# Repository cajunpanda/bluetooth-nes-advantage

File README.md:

# Bluetooth NES Advantage (v2)

Integrated Bluetooth for the NES Advantage (NES-026) arcade stick. It pairs directly with a
Nintendo Switch, an 8BitDo NES Retro Receiver (for a real NES), and PCs, phones, and emulators
over BLE. No case cutting and no added buttons: everything runs from the stick's own controls,
and it charges through the original cable hole.

**[Watch the overview and how-to video](https://youtu.be/xjbFiXHXB24)** for a tour of the mod and
everything below in use.

## Features

- Direct Nintendo Switch pairing (Switch Pro Controller emulation over BT Classic)
- Home, ZL + ZR (the NSO retro menu), ZL, ZR, and Capture — buttons the NES stick never had, on
  Select-held chords, instant and usable mid-game; the chord window is configurable, or off
- 8BitDo NES Retro Receiver support for playing on a real NES
- BLE gamepad mode for PC, Android, SteamOS, Linux, and BlueRetro
- Turbo and slow motion work as normal
- Player-select slider: in BLE mode the stick exposes two gamepads for take-turns play
- Wake on button press from a deep sleep that draws microamps
- Battery life on an 1800 mAh cell: about 17 hours in Switch/Receiver mode, about 37 hours in
  BLE mode, months of standby
- Low input latency: the board adds about 4 ms in Switch/Receiver mode and about 6 ms in BLE mode
- Browser-based configuration and over-the-air firmware updates, no cable needed
- RGB status LEDs, battery level monitoring, 5 V barrel jack charging
- Play while charging (load-share power path)

## Configure and update from your browser

A built-in Web Bluetooth app tests every input, tunes how the stick behaves, and flashes new
firmware over the air with no cable and nothing to install. Put the stick in config mode (hold
A + B + Select for 5 s), open the hosted
**[config page](https://cajunpanda.github.io/bluetooth-nes-advantage/)** in Chrome or Edge, and
connect. Every button, the D-pad, the player-select slider, and the turbo dials light up live as
you use them:

Change transport, button profile, and directional mode and apply over the air, or drop a
`firmware.bin` on the cartridge slot to update. The
[manual](docs/MANUAL.md#configuration-and-firmware-updates) has the full walkthrough.

## How it works

A single custom PCB replaces the controller's cable. A bare ESP32-WROOM-32E reads the original
CD4021 shift registers and presents the stick as a Bluetooth gamepad in one of two modes:

- Switch mode (Bluetooth Classic): emulates a Switch Pro Controller. Pairs directly with a
  Nintendo Switch and with the 8BitDo NES Retro Receiver.
- BLE mode: a standard BLE HID gamepad ("NES Advantage") for PCs, phones, BlueRetro, and
  emulators.

Turbo, slow motion, and the player-select slider all work as originally designed.

## Documentation

Start with the guide that fits you:

- **Using a modded controller:** [docs/MANUAL.md](docs/MANUAL.md). Pairing, gestures, LEDs, button
  profiles, two-player play, charging, and firmware updates.
- **Installing the mod in your controller:** [docs/INSTALL.md](docs/INSTALL.md). Wiring the harness,
  fitting the battery and board, insulating tape, and the 3D-printed jack plug.
- **Building your own kit:** [docs/HARDWARE.md](docs/HARDWARE.md). PCB, bill of materials, board
  assembly, and connection maps.
- **Building and customizing firmware:** [docs/FIRMWARE.md](docs/FIRMWARE.md). Toolchain, module
  layout, architecture, and the config/OTA path.

## Get one prebuilt

Complete kits and assembled boards are available at
[cajunpanda.com](https://cajunpanda.com/shop/bt-nes-advantage).

## Support

Questions and help: join the [Discord](https://discord.gg/t8uT8NgTnc).

## Repository layout

| Path                     | Contents                                                                  |
| ------------------------ | ------------------------------------------------------------------------- |
| [`firmware/`](firmware/) | ESP-IDF dual-mode Bluetooth firmware                                      |
| [`hardware/`](hardware/) | KiCad PCB project and the 3D-printable jack plug                          |
| [`web/`](web/)           | Web Bluetooth config and OTA update page                                  |
| [`tools/`](tools/)       | Serial monitor and build helpers                                          |
| [`docs/`](docs/)         | Manual, install guide, hardware guide, firmware guide, protocol reference |
| [`AGENTS.md`](AGENTS.md) | Working notes for contributors and AI coding agents                       |

## License

Licensed by medium: firmware and software under MIT, hardware (PCB and 3D models) under
CERN-OHL-P-2.0, documentation under CC-BY-4.0. See [LICENSING.md](LICENSING.md).

## PCBs

The PCBs for this product are sponsored and produced by PCBWay. As always, their service was amazing
and the fabrication as well as the shipping was fast. Because of the all-in-one customs and shipping
price, the handling of taxes and other fees was very easy.
[Click here](https://www.pcbway.com/project/shareproject/Bluetooth_NES_Advantage_865d24ef.html) to
order the PCBs from the shared project (gerbers preloaded).

## Disclaimer

This is an independent, unofficial project and is not affiliated with, endorsed by, sponsored by, or
associated with Nintendo Co., Ltd. Nintendo, NES, Nintendo Entertainment System, NES Advantage,
Nintendo Switch, and Nintendo Switch Pro Controller are trademarks of Nintendo. All trademarks are
the property of their respective owners and are used here only for identification and compatibility.
No Nintendo firmware, code, or assets are included; the Switch Pro Controller support is a clean-room
implementation of the controller's publicly documented behavior, for interoperability only.

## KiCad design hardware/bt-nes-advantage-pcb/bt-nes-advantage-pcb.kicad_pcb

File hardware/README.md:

# Hardware

Open hardware for the Bluetooth NES Advantage.

| Path | Contents |
|---|---|
| [`bt-nes-advantage-pcb/`](bt-nes-advantage-pcb/) | KiCad 10 PCB project (schematic and 2-layer layout) |
| [`bt-nes-advantage-jack-plug/`](bt-nes-advantage-jack-plug/) | 3D-printable DC jack plug (STL and FreeCAD source) |

The full build reference (architecture, BOM, pin and connection maps, power path, assembly, and
layout notes) is in [`../docs/HARDWARE.md`](../docs/HARDWARE.md). Pin assignments match the firmware
(`../firmware/main/board_config.h`).

Board highlights:

- **MCU:** bare ESP32-WROOM-32E-N4 on a single 3.3 V rail (the Advantage's logic runs at 3.3 V, so
  there is no 5 V rail and no level shifting).
- **Power:** barrel jack (+5 V) to TP4056 charger, 1S LiPo, discrete load-share power path, TPS63900
  buck-boost to 3.3 V. NES LATCH/CLK/DATA sit on RTC-capable GPIOs so the ULP polls the shift
  registers in deep sleep.
- **Programming and debug:** TC2030 Tag-Connect (J4), pinned for the TC2030-FTDI-C232HD-DDHSP-0-DTR
  USB-UART cable (DTR/RTS auto-reset). No onboard USB; charging is via the barrel jack only.
- **Status:** R/G/B 0603 LEDs (active-low), visible through the transparent jack plug.
- **Board:** 2 layer, 1.6 mm, 78 x 36 mm, fits the stock case with no cutting.

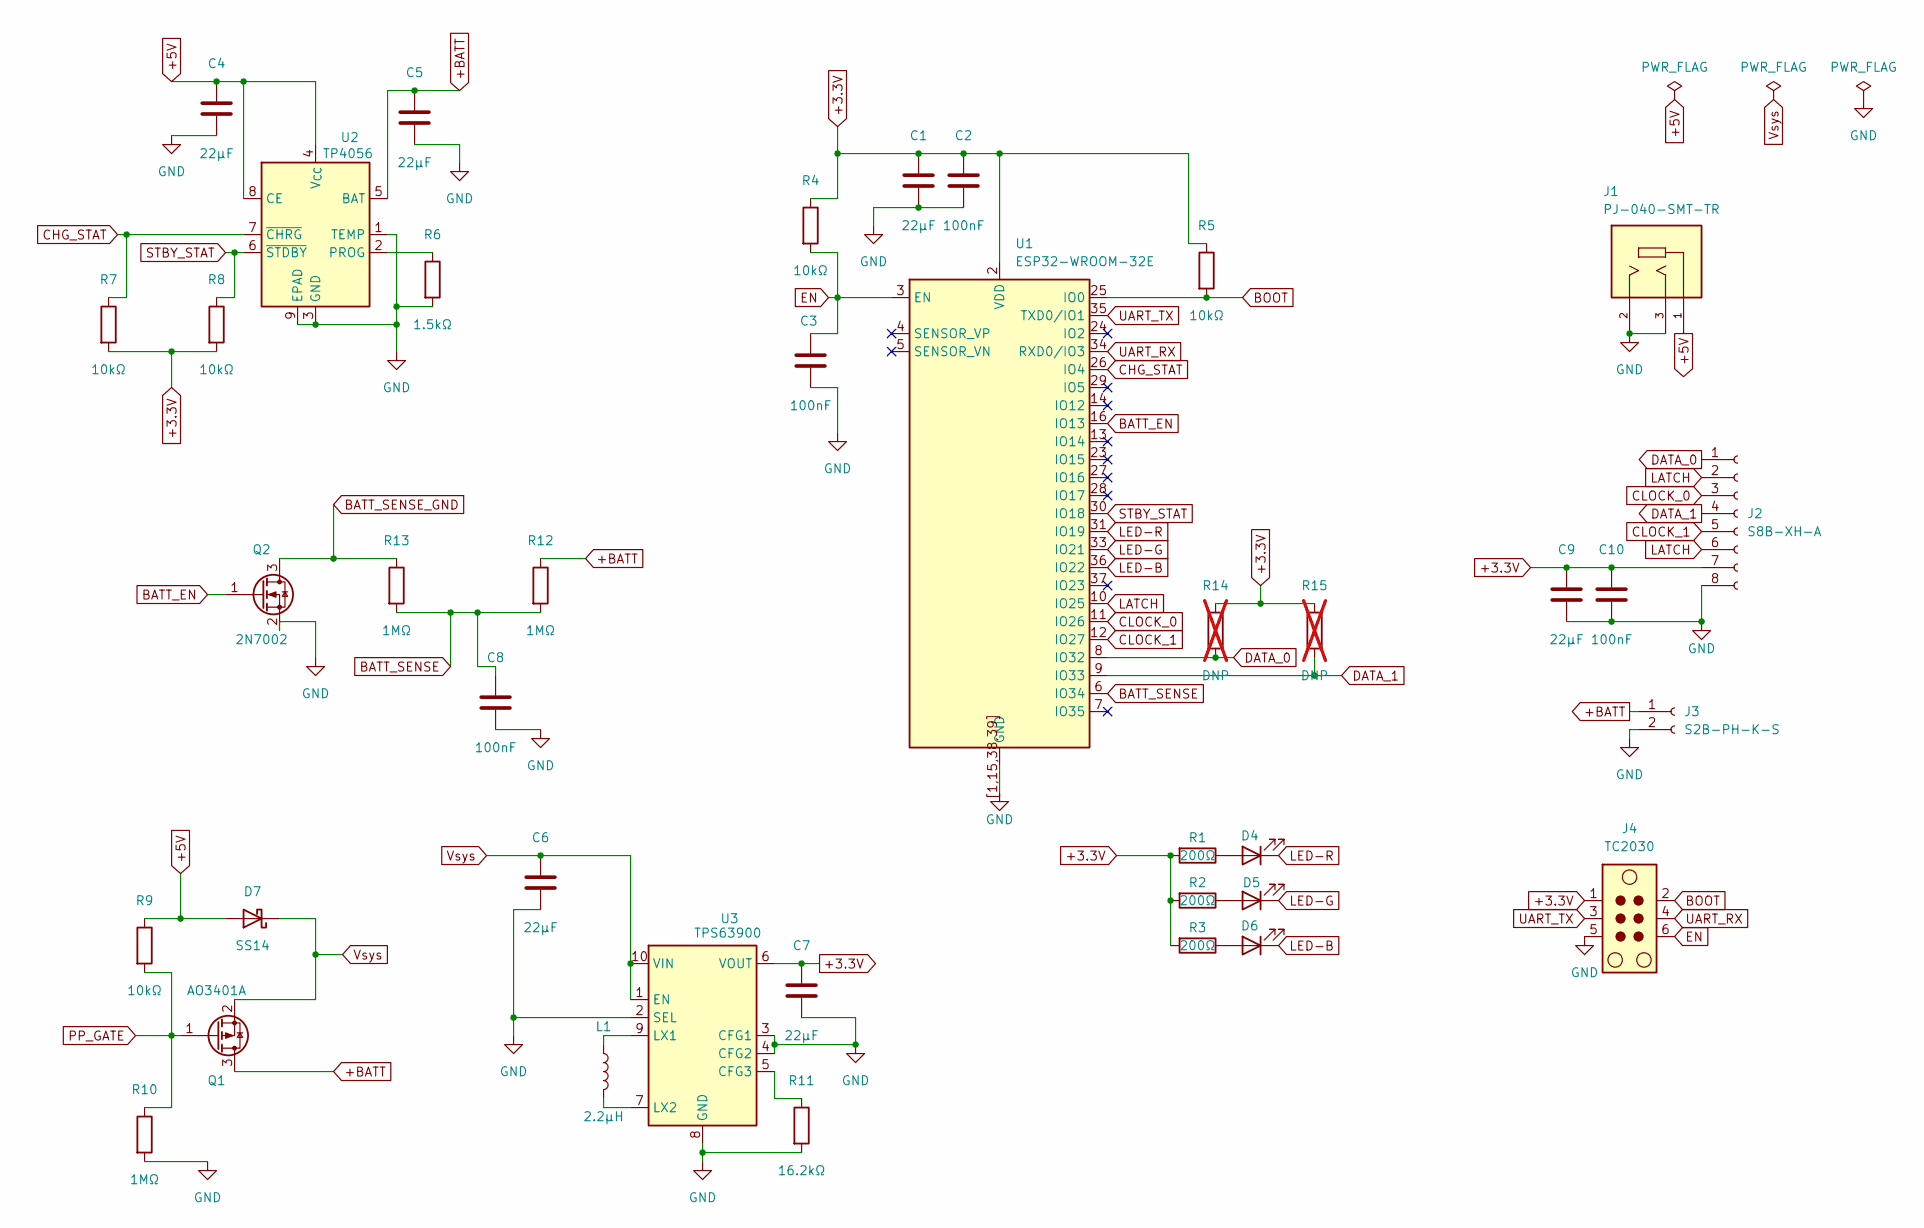
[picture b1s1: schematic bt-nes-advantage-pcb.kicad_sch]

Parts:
C1, C4, C5, C6, C7, C9: 22µF; C_0805_2012Metric_Pad1.18x1.45mm_HandSolder; MPN CL21A226KOQNNNE; LCSC C296720
C2, C3, C8, C10: 100nF; C_0603_1608Metric_Pad1.08x0.95mm_HandSolder; MPN CC0603KRX7R9BB104; LCSC C14663
D4: LTST-C193KRKT-5A; LED_0603_1608Metric_Pad1.05x0.95mm_HandSolder; MPN LTST-C193KRKT-5A; LCSC C157741
D5: LTST-C193KGKT-5A; LED_0603_1608Metric_Pad1.05x0.95mm_HandSolder; MPN LTST-C193KGKT-5A; LCSC C125102
D6: LTST-C193TBKT-5A; LED_0603_1608Metric_Pad1.05x0.95mm_HandSolder; MPN LTST-C193TBKT-5A; LCSC C125103
D7: SS14; D_SMA; MPN SS14; LCSC C2480
J1: PJ-040-SMT-TR; CUI_PJ-040-SMT-TR; MPN PJ-040-SMT-TR; Mouser Part Number 490-PJ-040-SMT-TR
J2: S8B-XH-A; JST_XH_S8B-XH-A_1x08_P2.50mm_Horizontal; MPN S8B-XH-A(LF)(SN); LCSC C157914
J3: S2B-PH-K-S; JST_PH_S2B-PH-K_1x02_P2.00mm_Horizontal; MPN S2B-PH-K-S(LF)(SN); LCSC C173752
J4: TC2030; Tag-Connect_TC2030-IDC-FP_2x03_P1.27mm_Vertical
L1: 2.2µH; L_Murata_DFE201610P; MPN DFE201610P-2R2M=P2; LCSC C237554
Q1: AO3401A; SOT-23; MPN AO3401A; LCSC C15127
Q2: 2N7002; SOT-23; MPN 2N7002; LCSC C8545
R1, R2, R3: 200Ω; R_0603_1608Metric_Pad0.98x0.95mm_HandSolder; MPN 0603WAF2000T5E; LCSC C8218
R4, R5, R7, R8, R9: 10kΩ; R_0603_1608Metric_Pad0.98x0.95mm_HandSolder; MPN 0603WAF1002T5E; LCSC C25804
R6: 1.5kΩ; R_0603_1608Metric_Pad0.98x0.95mm_HandSolder; MPN 0603WAF1501T5E; LCSC C22843
R10, R12, R13: 1MΩ; R_0603_1608Metric_Pad0.98x0.95mm_HandSolder; MPN 0603WAF1004T5E; LCSC C22935
R11: 16.2kΩ; R_0603_1608Metric_Pad0.98x0.95mm_HandSolder; MPN 0603WAF1622T5E; LCSC C22885
R14, R15: DNP; R_0603_1608Metric_Pad0.98x0.95mm_HandSolder; not fitted
U1: ESP32-WROOM-32E; MPN ESP32-WROOM-32E-N4; LCSC C701341
U2: TP4056; SOIC-8-1EP_3.9x4.9mm_P1.27mm_EP2.29x3mm_ThermalVias; MPN TP4056-42-ESOP8; LCSC C16581
U3: TPS63900; WSON-10-1EP_2.5x2.5mm_P0.5mm_EP1.2x2mm_ThermalVias; MPN TPS63900DSKR; LCSC C1518762

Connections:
+3.3V: C1.1, C2.1, C7.1, C9.1, C10.1, J2.7, J4.1, R1.2, R2.2, R3.2, R4.1, R5.1, R7.2, R8.2, R14.1, R15.1, U1.2 (VDD), U3.6 (VOUT)
+5V: C4.1, D7.2 (A), J1.1, R9.1, U2.4 (V_{CC}), U2.8 (CE)
+BATT: C5.1, J3.1, Q1.3 (D), R12.1, U2.5 (BAT)
BATT_EN: Q2.1 (G), U1.16 (IO13)
BATT_SENSE: C8.1, R12.2, R13.2, U1.6 (IO34)
BATT_SENSE_GND: Q2.3 (D), R13.1
BOOT: J4.2, R5.2, U1.25 (IO0)
CHG_STAT: R7.1, U1.26 (IO4), U2.7 (~CHRG)
CLOCK_0: J2.3, U1.11 (IO26)
CLOCK_1: J2.5, U1.12 (IO27)
DATA_0: J2.1, R14.2, U1.8 (IO32)
DATA_1: J2.4, R15.2, U1.9 (IO33)
EN: C3.1, J4.6, R4.2, U1.3 (EN)
GND: C1.2, C2.2, C3.2, C4.2, C5.2, C6.2, C7.2, C8.2, C9.2, C10.2, J1.2, J1.3, J2.8, J3.2, J4.5, Q2.2 (S), R6.2, R10.2, R11.2, U1.1 (GND), U1.15 (GND), U1.38 (GND), U1.39 (GND), U1.[1,15,38,39] (GND), U2.1 (TEMP), U2.3 (GND), U2.9 (EPAD), U3.2 (SEL), U3.3 (CFG1), U3.4 (CFG2), U3.8 (GND), U3.11 (GND)
LATCH: J2.2, J2.6, U1.10 (IO25)
LED-B: D6.1 (K), U1.36 (IO22)
LED-G: D5.1 (K), U1.33 (IO21)
LED-R: D4.1 (K), U1.31 (IO19)
unnamed: D4.2 (A), R1.1
unnamed: D5.2 (A), R2.1
unnamed: D6.2 (A), R3.1
unnamed: R6.1, U2.2 (PROG)
unnamed: R11.1, U3.5 (CFG3)
unnamed: L1.1, U3.9 (LX1)
unnamed: L1.2, U3.7 (LX2)
PP_GATE: Q1.1 (G), R9.2, R10.1
STBY_STAT: R8.1, U1.30 (IO18), U2.6 (~STDBY)
UART_RX: J4.4, U1.34 (RXD0/IO3)
UART_TX: J4.3, U1.35 (TXD0/IO1)
Vsys: C6.1, D7.1 (K), Q1.2 (S), U3.1 (EN), U3.10 (VIN)

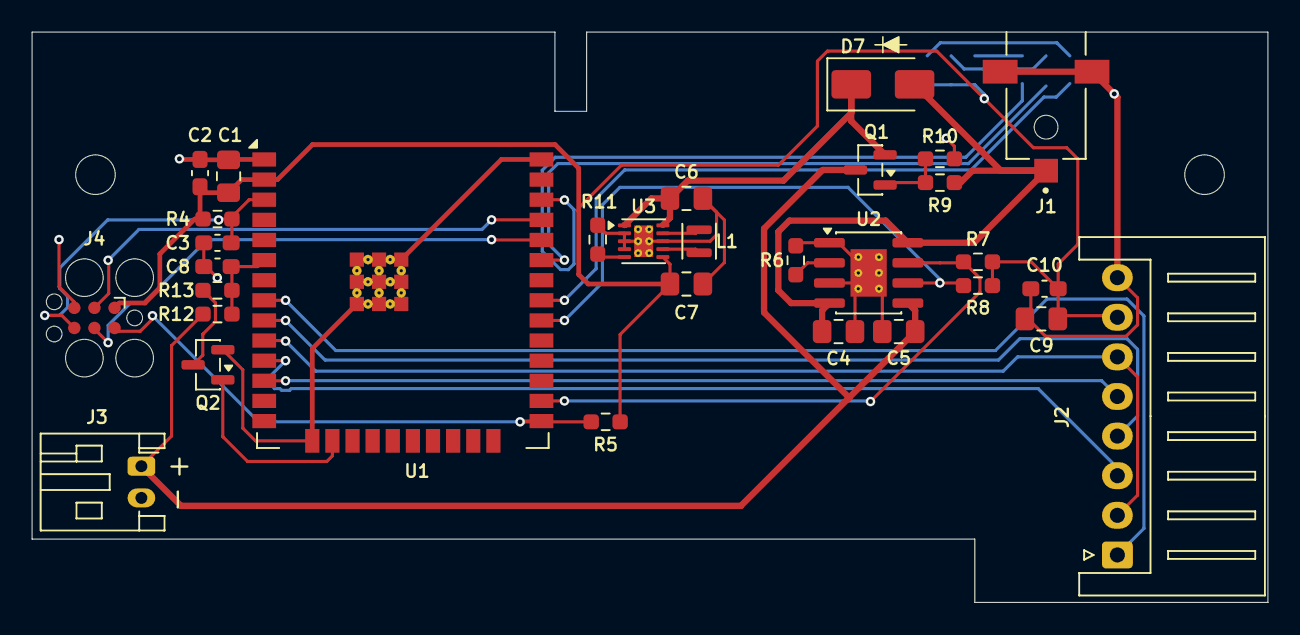
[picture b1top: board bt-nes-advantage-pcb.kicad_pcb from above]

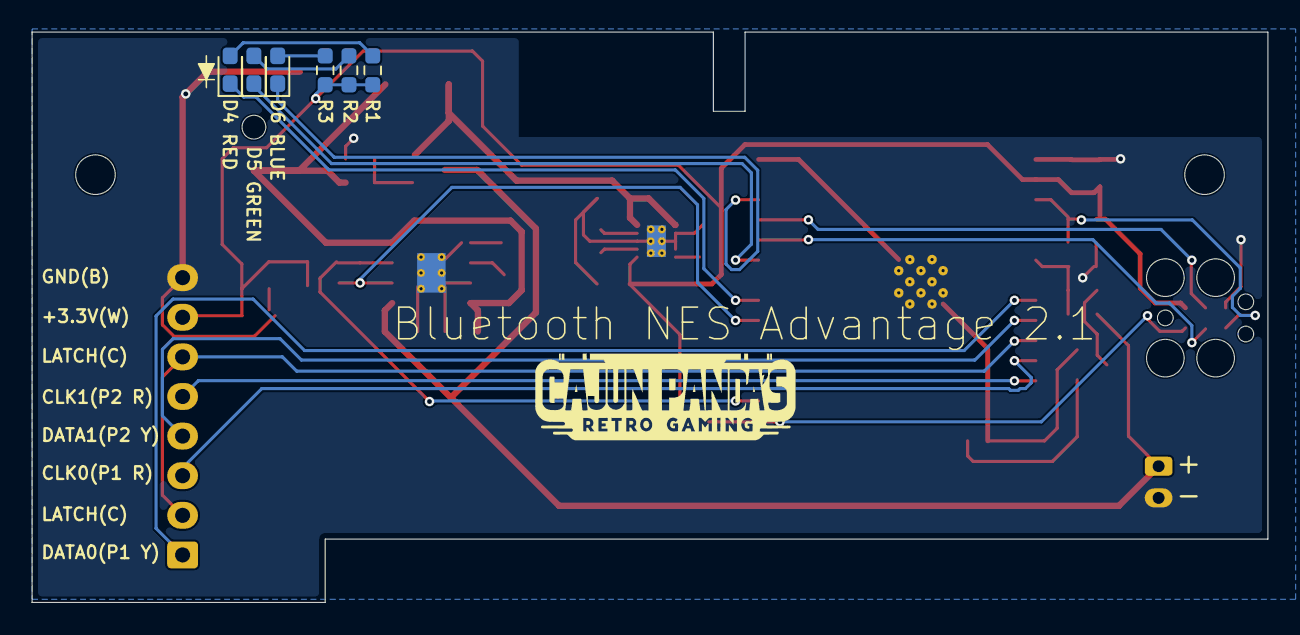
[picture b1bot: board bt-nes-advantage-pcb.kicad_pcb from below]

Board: 2 copper layers, 78.0 x 36.0 mm, 37 parts (6 on the bottom side), 30 nets.

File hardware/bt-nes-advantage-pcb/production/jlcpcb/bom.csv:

Comment,Designator,Footprint,LCSC Part #
22uF,"C1,C4,C5,C6,C7,C9",C_0805_2012Metric_Pad1.18x1.45mm_HandSolder,C45783
100nF,"C2,C3,C8,C10",C_0603_1608Metric_Pad1.08x0.95mm_HandSolder,C14663
LTST-C193KRKT-5A,D4,LED_0603_1608Metric_Pad1.05x0.95mm_HandSolder,C157741
LTST-C193KGKT-5A,D5,LED_0603_1608Metric_Pad1.05x0.95mm_HandSolder,C125102
LTST-C193TBKT-5A,D6,LED_0603_1608Metric_Pad1.05x0.95mm_HandSolder,C125103
SS14,D7,D_SMA,C2480
2.2uH,L1,L_Murata_DFE201610P,C237554
AO3401A,Q1,SOT-23,C15127
2N7002,Q2,SOT-23,C8545
200R,"R1,R2,R3",R_0603_1608Metric_Pad0.98x0.95mm_HandSolder,C8218
10k,"R4,R5,R7,R8,R9",R_0603_1608Metric_Pad0.98x0.95mm_HandSolder,C25804
1.5k,R6,R_0603_1608Metric_Pad0.98x0.95mm_HandSolder,C22843
1M,"R10,R12,R13",R_0603_1608Metric_Pad0.98x0.95mm_HandSolder,C22935
16.2k,R11,R_0603_1608Metric_Pad0.98x0.95mm_HandSolder,C22885
ESP32-WROOM-32E,U1,ESP32-WROOM-32E,C701341
TP4056,U2,SOIC-8-1EP_3.9x4.9mm_P1.27mm_EP2.29x3mm_ThermalVias,C16581
TPS63900,U3,WSON-10-1EP_2.5x2.5mm_P0.5mm_EP1.2x2mm_ThermalVias,C1518762

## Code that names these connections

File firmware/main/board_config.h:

// SPDX-License-Identifier: MIT
// Copyright 2026 Aaron Perkins

#pragma once
#include "driver/gpio.h"

// Pin map for the production PCB (see docs/HARDWARE.md). Constraint: NES LATCH/CLK/DATA must be
// RTC-capable so the ULP can poll the 4021 in deep sleep. LATCH/CLK need RTC OUTPUT-capable pins
// (25/26/27/32/33). DATA stays on 32/33 (they have internal pulls; GPIO34-39 are input-only with
// no pulls). Avoid strapping pins; never use GPIO12. Battery sense must be ADC1 (32-39); ADC2 is
// unusable while the radio is on.

// Reserved for programming (do not reuse): U0TXD=GPIO1, U0RXD=GPIO3, plus EN + IO0 (auto-reset).
// These route to the TC2030 Tag-Connect footprint (J4), pinned for the
// TC2030-FTDI-C232HD-DDHSP-0-DTR USB-UART cable (DTR drives IO0, RTS drives EN for esptool reset).
// Charging is via the barrel jack (J1, +5V) only, no onboard USB.

// NES Advantage serial interface (CD4021)
#define NES_LATCH       GPIO_NUM_25   // RTC, output
#define NES_CLK_P1      GPIO_NUM_26   // RTC, output
#define NES_CLK_P2      GPIO_NUM_27   // RTC, output
#define NES_DATA_P1     GPIO_NUM_32   // RTC, input + pull-up
#define NES_DATA_P2     GPIO_NUM_33   // RTC, input + pull-up

// Battery sense (resistor divider), ADC1
#define BATTERY_ADC_GPIO GPIO_NUM_34  // ADC1_CH6, input-only
#define BATT_EN          GPIO_NUM_13  // Q2 gate: drive HIGH to ground the divider while sampling,
                                      // LOW in deep sleep so the 1M/1M divider draws ~0

// Status LEDs (active-low)
#define LED_RED         GPIO_NUM_19
#define LED_GREEN       GPIO_NUM_21
#define LED_BLUE        GPIO_NUM_22

// Charger status pins (TP4056, open-drain active-low; R7/R8 pull them up to +3.3V on the board)
//
// CHG_STAT is the one pin that moved between board revisions: PCB 2.1 put it on an RTC-capable GPIO
// so the charger can wake the SoC out of deep sleep, which GPIO23 cannot do. Both candidates are
// listed here and the wired one is resolved at runtime, so a single build runs on either board.
// Use board::chg_stat_gpio(), never these constants directly.
#define CHG_STAT_REV20  GPIO_NUM_23   // charging, PCB 2.0: not RTC-capable, so no charger wake
#define CHG_STAT_REV21  GPIO_NUM_4    // charging, PCB 2.1: RTC, ext1 wakes on charger insert
#define STBY_STAT       GPIO_NUM_18   // standby / full, both revisions

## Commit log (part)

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2026-06-22 Initial public release
    Open hardware and firmware that adds integrated Bluetooth to an NES Advantage (NES-026) arcade stick: Switch Pro Controller emulation over BT Classic, BLE HID gamepad, 8BitDo Retro Receiver support, 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
    Contents: ESP-IDF firmware (firmware/), KiCad PCB and 3D jack-plug model (hardware/), Web Bluetooth config/OTA page (web/), host tools (tools/), and docs (docs/). Licensed per medium: MIT for code, C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
